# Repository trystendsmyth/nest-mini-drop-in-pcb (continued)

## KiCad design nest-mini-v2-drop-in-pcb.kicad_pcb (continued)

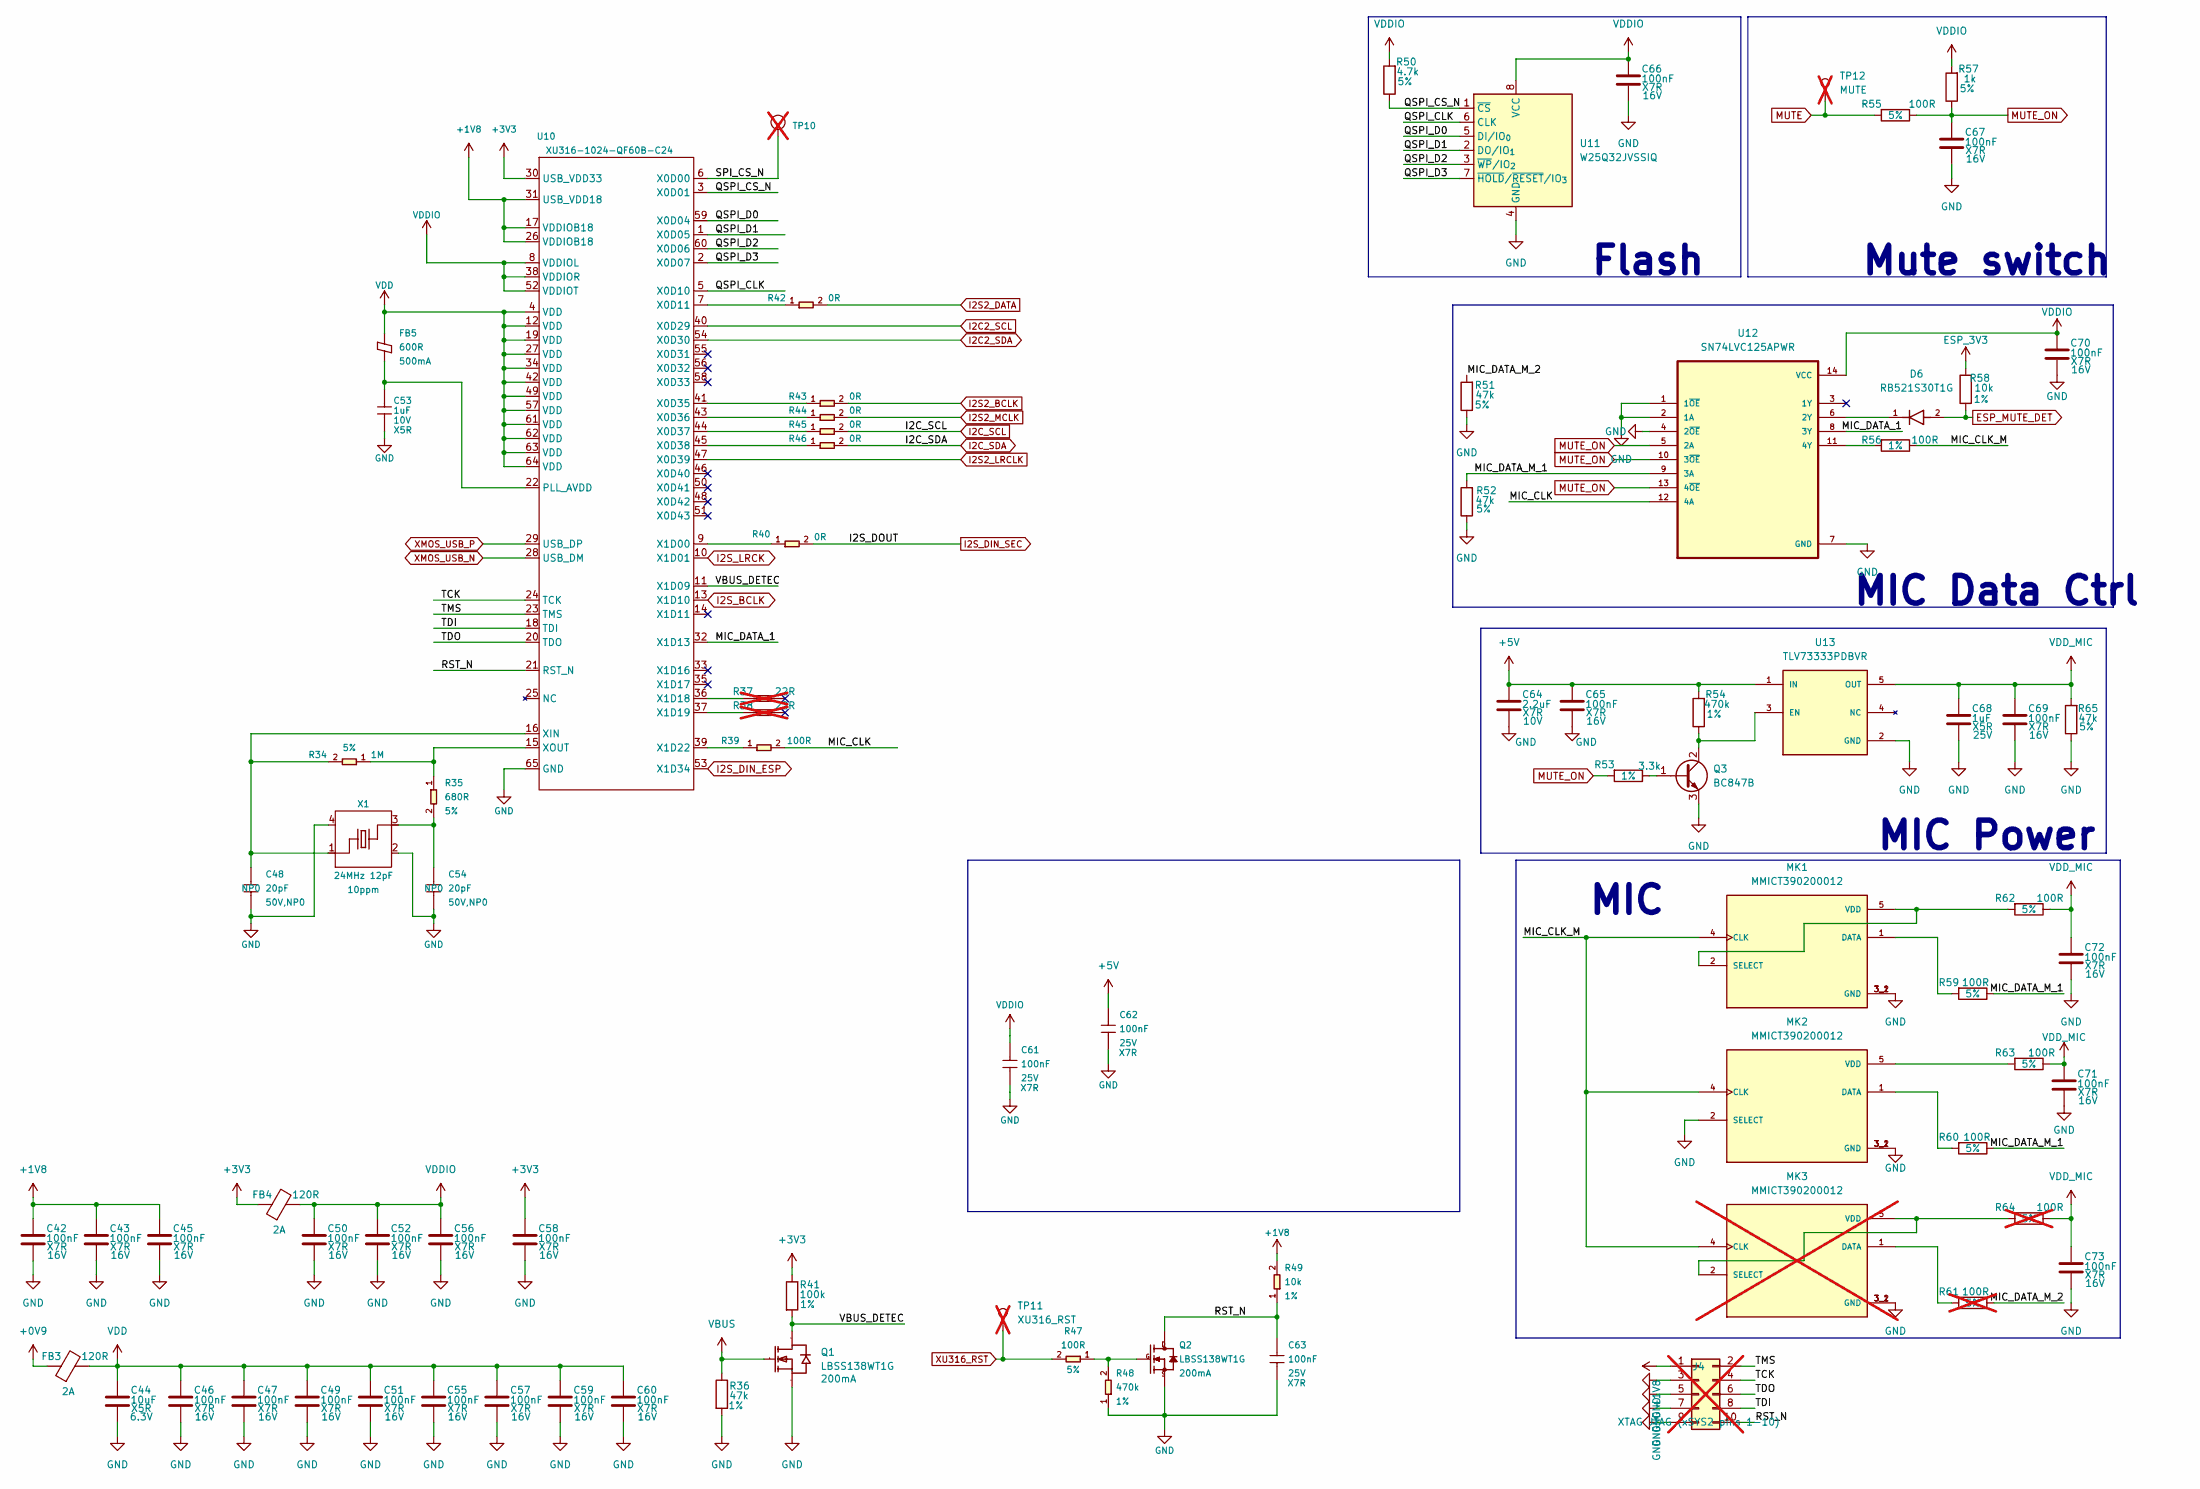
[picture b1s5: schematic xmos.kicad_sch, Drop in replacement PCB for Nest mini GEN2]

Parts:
C42, C43, C45, C46, C47, C49, C50, C51, C52, C55, C56, C57, C58, C59, C60, C65, C66, C67, C69, C70, C71, C72, C73: 100nF; C_0402_1005Metric; Voltage 16V; Manufacturer Part CL05B104KO5NNNC; LCSC Part # C1525
C44: 10uF; C_0402_1005Metric; Voltage 6.3V; Manufacturer Part CL05A106MQ5NUNC; LCSC Part # C15525
C48, C54: 20pF; C_0402_1005Metric; Voltage Rating 50V,NP0; Voltage 50V; MPN 0402CG200J500NT; LCSC Part # C1554
C53: 1uF; C_0402_1005Metric; Voltage Rating 10V; Voltage 25V; MPN CL05A105KA5NQNC; LCSC Part # C52923
C61, C62: 100nF; C_0402_1005Metric; Voltage Rating 25V; Voltage 16V; MPN CL05B104KO5NNNC; LCSC Part # C1525
C63: 100nF; C_0402_1005Metric; Voltage Rating 25V; MPN CC0402KRX7R8BB104; LCSC Part # C1525
C64: 2.2uF; C_0603_1608Metric; Voltage 10V; Manufacturer Part GRM188R71A225KE15D; LCSC Part # C86018
C68: 1uF; C_0402_1005Metric; Voltage 25V; Manufacturer Part CL05A105KA5NQNC; LCSC Part # C52923
D6: RB521S30T1G; DIOM168X70N; PARTREV 7/11/1905; LCSC Part # C27636108
FB3: 120R; BLM18PG121SN1D; Part number BLM18PG121SN1D; LCSC Part # C14709
FB4: 120R; BLM18PG121SN1D; Part number BLM18AG121SN1D; LCSC Part # C14709
FB5: 600R; BLM18PG121SN1D; Rating 500mA; MPN BLM18KG601SN1D; LCSC Part # C85833
J4: XTAG JTAG (xSYS2 pins 1-10); PinHeader_2x05_P1.27mm_Vertical; not fitted
MK1, MK2: MMICT390200012; MIC_T3902; PARTREV 1.0; LCSC Part # C3171752
MK3: MMICT390200012; MIC_T3902; PARTREV 1.0; LCSC Part # C3171752; not fitted
Q1: LBSS138WT1G; SC-70-3_L2.1-W1.3-P0.65-LS2.1-BR; Manufacturer Part LBSS138WT1G; LCSC Part # C383201
Q2: LBSS138WT1G; SOT-323_SC-70; Rating 200mA; MPN LBSS138WT1G; LCSC Part # C383201
Q3: BC847B; SOT-23; Manufacturer Part BC847B; LCSC Part # C20069135
R34: 1M; R_0402_1005Metric; Power Rating 5%; MPN 0402WGF1004TCE; LCSC Part # C26083
R35: 680R; R_0402_1005Metric; Power Rating 5%; MPN 0402WGF6800TCE; LCSC Part # C25130
R36: 47k; R_0402_1005Metric; Tolerance 1%; Manufacturer Part 0402WGF4702TCE; LCSC Part # C25792
R37, R38: 22R; R_0402_1005Metric; Power Rating 5%; MPN 0402WGF220JTCE; LCSC Part # C25092; not fitted
R39: 100R; R_0402_1005Metric; Power Rating 5%; MPN 0402WGF1000TCE; LCSC Part # C25076
R40, R43, R44, R45, R46: 0R; R_0402_1005Metric; Power Rating 5%; MPN 0402WGF0000TCE; LCSC Part # C17168
R41: 100k; R_0402_1005Metric; Tolerance 1%; Manufacturer Part 0402WGJ0104TCE; LCSC Part # C25530
R42: 0R; R_0402_1005Metric; Tolerance 5%; MPN 0402WGF0000TCE; LCSC Part # C17168
R47: 100R; R_0402_1005Metric; Power Rating 5%; MPN RC0402JR-07100RL; LCSC Part # C25076
R48: 470k; R_0402_1005Metric; Power Rating 1%; MPN RC0402FR-07470KL; LCSC Part # C25790
R49: 10k; R_0402_1005Metric; Power Rating 1%; MPN RC0402FR-0710KL; LCSC Part # C25744
R50: 4.7k; R_0402_1005Metric; Tolerance 5%; Manufacturer Part 0402WGF4701TCE; LCSC Part # C25900
R51, R52, R65: 47k; R_0402_1005Metric; Tolerance 5%; Manufacturer Part 0402WGF4702TCE; LCSC Part # C25792
R53: 3.3k; R_0402_1005Metric; Tolerance 1%; Manufacturer Part 0402WGF3301TCE; LCSC Part # C25890
R54: 470k; R_0402_1005Metric; Tolerance 1%; Manufacturer Part 0402WGF4703TCE; LCSC Part # C25790
R55, R59, R60, R62, R63: 100R; R_0402_1005Metric; Tolerance 5%; Manufacturer Part 0402WGF1000TCE; LCSC Part # C25076
R56: 100R; R_0402_1005Metric; Tolerance 1%; Manufacturer Part 0402WGF1000TCE; LCSC Part # C25076
R57: 1k; R_0402_1005Metric; Tolerance 5%; Manufacturer Part 0402WGF1001TCE; LCSC Part # C11702
R58: 10k; R_0402_1005Metric; Tolerance 1%; Manufacturer Part 0402WGF1002TCE; LCSC Part # C25744
R61, R64: 100R; R_0402_1005Metric; Tolerance 5%; Manufacturer Part 0402WGF1000TCE; LCSC Part # C25076; not fitted
TP10: TEST-POINT; TestPoint_Pad_D1.0mm; not fitted
TP11: XU316_RST; TestPoint_Pad_D1.0mm; not fitted
TP12: MUTE; TestPoint_Pad_D1.0mm; not fitted
U10: XU316-1024-QF60B-C24​; XU316-1024-QF60B-C24; MPN XU316-1024-QF60B-C24; LCSC Part # C6617472
U11: W25Q32JVSSIQ; SOIC-8_5.3x5.3mm_P1.27mm; Manufacturer Part W25Q32JVSSIQ; LCSC Part # C179173
U12: SN74LVC125APWR; SOP65P640X120-14N; Manufacturer Part SN74LVC125APWR; LCSC Part # C7813
U13: TLV73333PDBVR; PARTREV C; LCSC Part # C134139
X1: 24MHz 12pF; X4-SMD-2.0X1.6MM; Rating 10ppm; MPN 7F24000E12UCG; LCSC Part # C252273

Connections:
+0V9: FB3.1; also elsewhere on the board
+1V8: C42.1, C43.1, C45.1, J4.1, R49.2, U10.17 (VDDIOB18), U10.26 (VDDIOB18), U10.31 (USB_VDD18); also elsewhere on the board
+3V3: C58.1, FB4.1, R41.1, U10.30 (USB_VDD33); also elsewhere on the board
+5V: C62.1, C64.1, C65.1, R54.2, U13.1 (IN); also elsewhere on the board
/XMOS/MIC_CLK: R39.2, U12.12 (4A)
/XMOS/MIC_CLK_M: MK1.4 (CLK), MK2.4 (CLK), MK3.4 (CLK), R56.1
/XMOS/MIC_DATA_1: U10.32 (X1D13), U12.8 (3Y)
/XMOS/MIC_DATA_M_1: R52.2, R59.1, R60.1, U12.9 (3A)
/XMOS/MIC_DATA_M_2: R51.2, R61.1
/XMOS/QSPI_CLK: U10.5 (X0D10), U11.6 (CLK)
/XMOS/QSPI_CS_N: R50.1, U10.3 (X0D01), U11.1 (~CS)
/XMOS/QSPI_D0: U10.59 (X0D04), U11.5 (DI/IO_{0})
/XMOS/QSPI_D1: U10.1 (X0D05), U11.2 (DO/IO_{1})
/XMOS/QSPI_D2: U10.60 (X0D06), U11.3 (~WP/IO_{2})
/XMOS/QSPI_D3: U10.2 (X0D07), U11.7 (~HOLD/~RESET/IO_{3})
/XMOS/RST_N: C63.1, J4.10, Q2.3 (D), R49.1, U10.21 (RST_N)
/XMOS/SPI_CS_N: TP10.1 (T), U10.6 (X0D00)
/XMOS/TCK: J4.4, U10.24 (TCK)
/XMOS/TDI: J4.8, U10.18 (TDI)
/XMOS/TDO: J4.6, U10.20 (TDO)
/XMOS/TMS: J4.2, U10.23 (TMS)
/XMOS/VBUS_DETEC: Q1.3 (D), R41.2, U10.11 (X1D09)
ESP_3V3: R58.2; also elsewhere on the board
ESP_MUTE_DET: D6.2, R58.1; also elsewhere on the board
GND: C42.2, C43.2, C44.2, C45.2, C46.2, C47.2, C48.2, C49.2, C50.2, C51.2, C52.2, C53.2, C54.2, C55.2, C56.2, C57.2, C58.2, C59.2, C60.2, C61.2, C62.2, C63.2, C64.2, C65.2, C66.2, C67.2, C68.2, C69.2, C70.2, C71.2, C72.2, C73.2, J4.3, J4.5, J4.7, J4.9, MK1.3_1 (GND), MK1.3_2 (GND), MK2.2 (SELECT), MK2.3_1 (GND), MK2.3_2 (GND), MK3.3_1 (GND), MK3.3_2 (GND), Q1.2 (S), Q2.2 (S), Q3.3 (E), R36.2, R48.1, R51.1, R52.1, R65.1, U10.65 (GND), U11.4 (GND), U12.1 (1~OE), U12.2 (1A), U12.4 (2~OE), U12.7 (GND), U13.2 (GND), X1.2, X1.4; also elsewhere on the board
I2C2_SCL: U10.40 (X0D29)
I2C2_SDA: U10.54 (X0D30)
I2C_SCL: R45.2; also elsewhere on the board
I2C_SDA: R46.2; also elsewhere on the board
I2S2_BCLK: R43.2; also elsewhere on the board
I2S2_DATA: R42.2; also elsewhere on the board
I2S2_LRCLK: U10.47 (X0D39); also elsewhere on the board
I2S2_MCLK: R44.2; also elsewhere on the board
I2S_BCLK: U10.13 (X1D10); also elsewhere on the board
I2S_DIN_ESP: U10.53 (X1D34); also elsewhere on the board
I2S_DIN_SEC: R40.2; also elsewhere on the board
I2S_LRCK: U10.10 (X1D01); also elsewhere on the board
MUTE: R55.2, TP12.1; also elsewhere on the board
MUTE_ON: C67.1, R53.2, R55.1, R57.1, U12.5 (2A), U12.10 (3~OE), U12.13 (4~OE)
unnamed: C54.1, R35.2, X1.3
unnamed: MK1.1 (DATA), R59.2
unnamed: MK1.2 (SELECT), MK1.5 (VDD), R62.2
unnamed: MK2.1 (DATA), R60.2
unnamed: MK2.5 (VDD), R63.2
unnamed: MK3.1 (DATA), R61.2
unnamed: MK3.2 (SELECT), MK3.5 (VDD), R64.2
unnamed: Q2.1 (G), R47.1, R48.2
unnamed: Q3.1 (B), R53.1
unnamed: Q3.2 (C), R54.1, U13.3 (EN)
unnamed: C53.1, FB5.1, U10.22 (PLL_AVDD)
unnamed: R42.1, U10.7 (X0D11)
unnamed: R43.1, U10.41 (X0D35)
unnamed: R44.1, U10.43 (X0D36)
unnamed: R45.1, U10.44 (X0D37)
unnamed: R46.1, U10.45 (X0D38)
unnamed: R40.1, U10.9 (X1D00)
unnamed: R37.1, U10.36 (X1D18)
unnamed: R38.1, U10.37 (X1D19)
unnamed: R39.1, U10.39 (X1D22)
unnamed: C48.1, R34.2, U10.16 (XIN), X1.1
unnamed: R34.1, R35.1, U10.15 (XOUT)
unnamed: D6.1, U12.6 (2Y)
unnamed: R56.2, U12.11 (4Y)
VBUS: Q1.1 (G), R36.1; also elsewhere on the board
VDD: C44.1, C46.1, C47.1, C49.1, C51.1, C55.1, C57.1, C59.1, C60.1, FB3.2, FB5.2, U10.4 (VDD), U10.12 (VDD), U10.19 (VDD), U10.27 (VDD), U10.34 (VDD), U10.42 (VDD), U10.49 (VDD), U10.57 (VDD), U10.61 (VDD), U10.62 (VDD), U10.63 (VDD), U10.64 (VDD)
VDDIO: C50.1, C52.1, C56.1, C61.1, C66.1, C70.1, FB4.2, R50.2, R57.2, U10.8 (VDDIOL), U10.38 (VDDIOR), U10.52 (VDDIOT), U11.8 (VCC), U12.14 (VCC)
VDD_MIC: C68.1, C69.1, C71.1, C72.1, C73.1, R62.1, R63.1, R64.1, R65.2, U13.5 (OUT)
XMOS_USB_N: U10.28 (USB_DM); also elsewhere on the board
XMOS_USB_P: U10.29 (USB_DP); also elsewhere on the board
XU316_RST: R47.2, TP11.1; also elsewhere on the board

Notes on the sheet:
Flash
MIC
Mute switch
MIC Power
MIC Data Ctrl

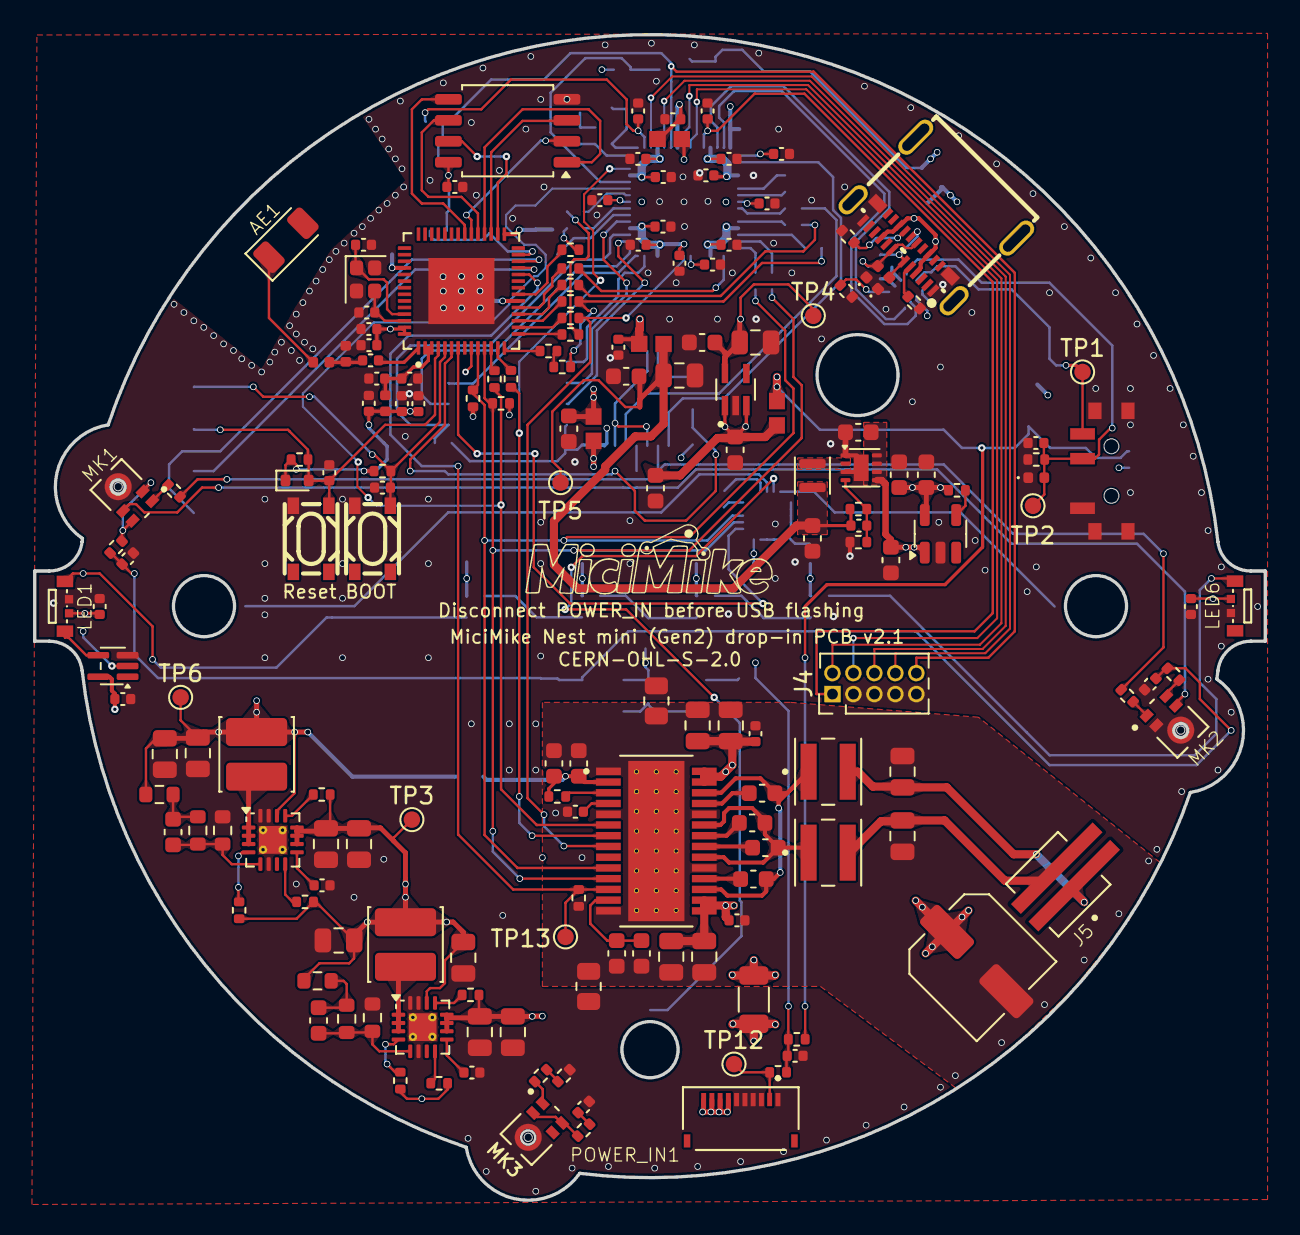
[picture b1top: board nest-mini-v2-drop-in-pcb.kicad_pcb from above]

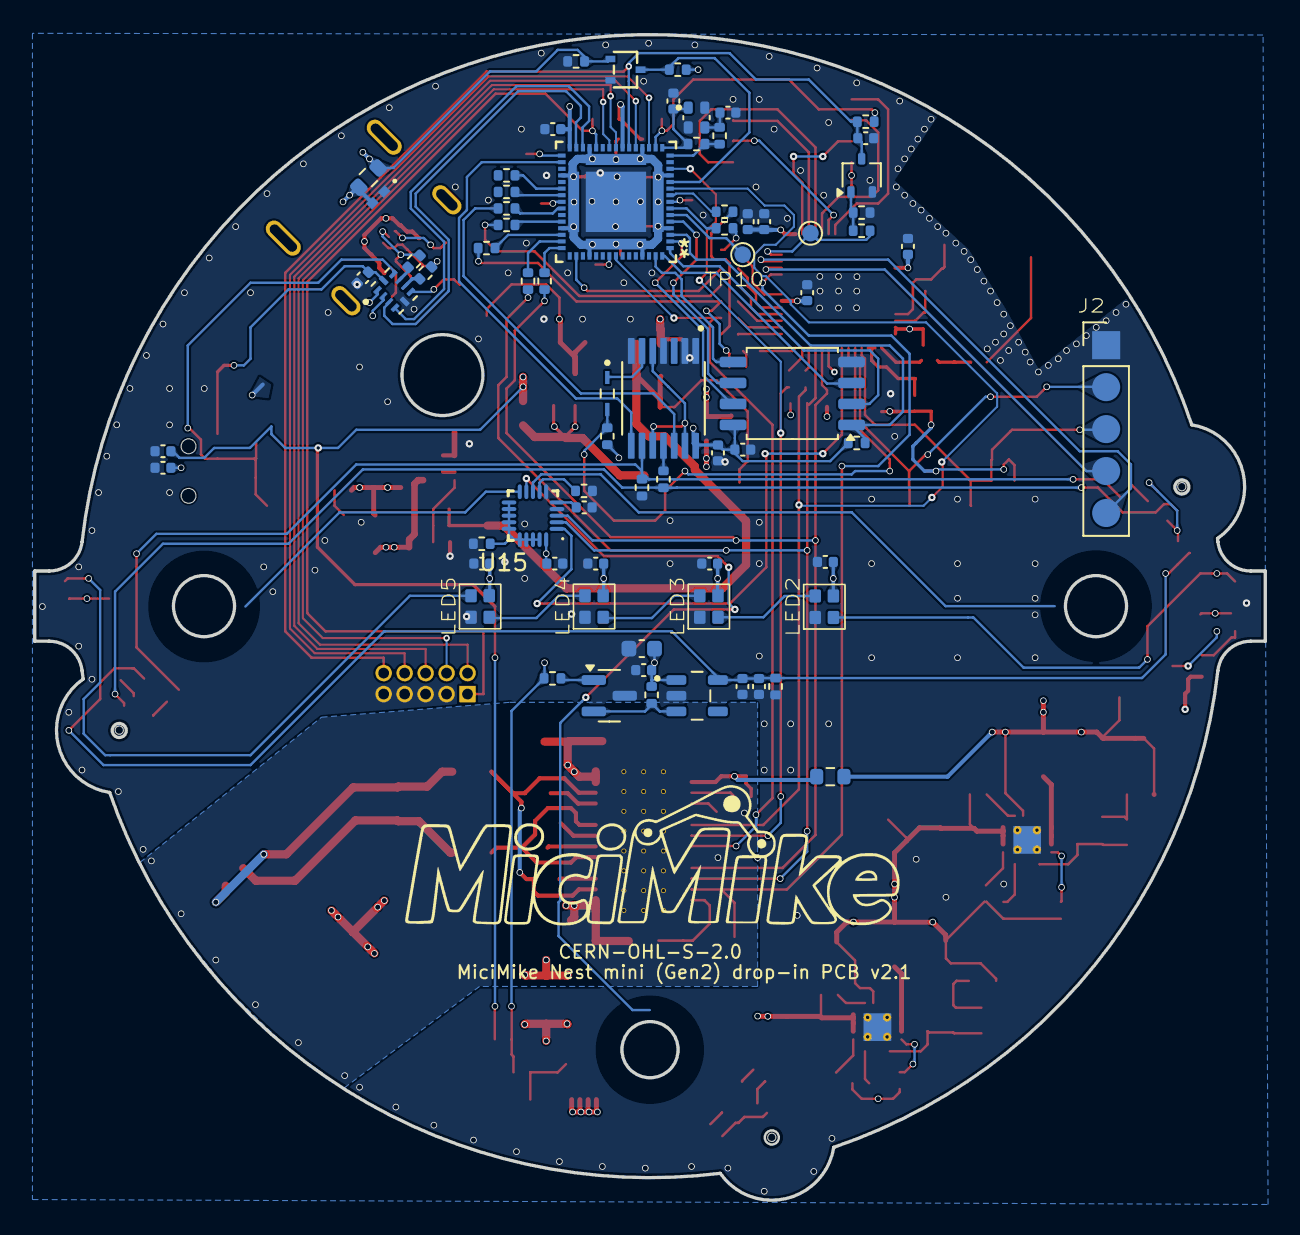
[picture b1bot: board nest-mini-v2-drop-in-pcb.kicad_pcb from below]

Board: 4 copper layers, 74.5 x 70.6 mm, 245 parts (71 on the bottom side), 147 nets.

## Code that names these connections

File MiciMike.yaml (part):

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
i2c:
  - id: internal_i2c
    sda: GPIO5
    scl: GPIO6
    frequency: 400kHz

psram:
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    id: hardware_mute_switch
    internal: true
    pin:
      number: GPIO1   # ESP_MUTE_DET (10k pull-up on board)
      mode: INPUT
    on_press:
      # Play mute on sound only if software mute isn't enabled
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  # Hardware LED ring. Not used because remapping needed
  - platform: esp32_rmt_led_strip
    id: leds_internal
    pin: GPIO4    # ESP_WS2812 -> U16 level shifter -> LED ring (v2.1: moved from GPIO21)
    chipset: SK6812
    max_refresh_rate: 15ms
    num_leds: 6
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voice_kit:
  id: voice_kit_component
  i2c_id: internal_i2c
  reset_pin: GPIO21   # XU316_RST (drives Q2 -> XMOS RST_N); v2.1: moved from GPIO17
  firmware:
    url: https://github.com/esphome/voice-kit-xmos-firmware/releases/download/v1.3.1/ffva_v1.3.1_upgrade.bin
    version: "1.3.1"
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    i2c_id: internal_i2c
    address: 0x2D          # R70 = 15k from ADR/FAULT to DVDD (TAS5805M datasheet table 7-5)
    tas58xx_dac: TAS5805M
    enable_pin: GPIO18     # AUDIO_PA_EN -> PDN (47k pull-down)
    dac_mode: PBTL         # OUT_A/OUT_B are paralleled on this board
    mixer_mode: MONO
    # PVDD is 14 V but the Nest Mini driver is small: start at the lowest analog gain
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
i2s_audio:
  - id: i2s_output
    # i2s_output data pin is gpio10
    i2s_lrclk_pin:
      number: GPIO7
    i2s_bclk_pin:
      number: GPIO8

  - id: i2s_input
    # data line is GPIO15
    i2s_lrclk_pin:
      number: GPIO14
    i2s_bclk_pin:
      number: GPIO13

microphone:
  - platform: i2s_audio
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    id: i2s_audio_speaker
    sample_rate: 48000
    i2s_mode: secondary
    i2s_dout_pin: GPIO10    # playback into XMOS X1D00 (AEC reference); XMOS forwards to the amp
    bits_per_sample: 32bit
    i2s_audio_id: i2s_output
    dac_type: external
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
